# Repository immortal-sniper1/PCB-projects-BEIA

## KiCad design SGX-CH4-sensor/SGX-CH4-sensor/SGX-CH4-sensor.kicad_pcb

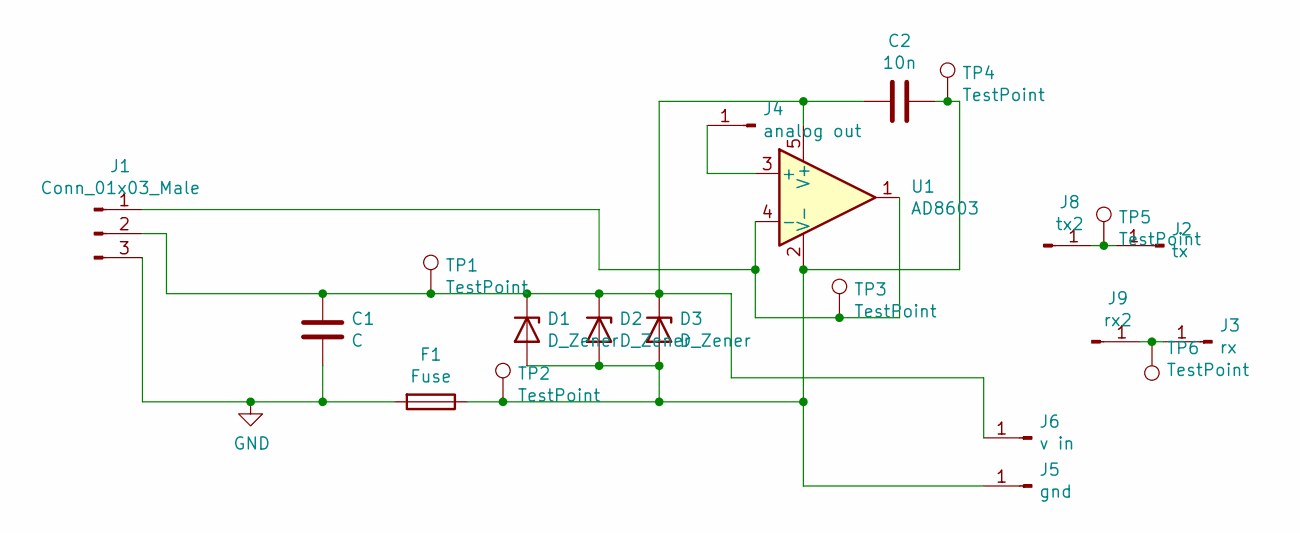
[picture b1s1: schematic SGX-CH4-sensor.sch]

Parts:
C1: C; CP_Radial_D8.0mm_P5.00mm
C2: 10n; CP_Radial_D6.3mm_P2.50mm
D1, D2, D3: D_Zener; D_DO-35_SOD27_P10.16mm_Horizontal
F1: Fuse; R_Axial_DIN0309_L9.0mm_D3.2mm_P5.08mm_Vertical
J1: Conn_01x03_Male; PinHeader_1x03_P2.54mm_Vertical
J2: tx; PinHeader_1x01_P2.54mm_Vertical
J3: rx; PinHeader_1x01_P2.54mm_Vertical
J4: analog out; PinHeader_1x01_P2.54mm_Vertical
J5: gnd; PinHeader_1x01_P2.54mm_Vertical
J6: v in; PinHeader_1x01_P2.54mm_Vertical
J8: tx2; PinHeader_1x01_P2.54mm_Vertical
J9: rx2; PinHeader_1x01_P2.54mm_Vertical
TP1, TP2, TP3, TP4, TP5, TP6: TestPoint; TestPoint_Pad_D3.0mm
U1: AD8603; SOT-23-5

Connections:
GND: C1.2, F1.2, J1.3
unnamed: C1.1, C2.1, D1.1 (K), D2.1 (K), D3.1 (K), J1.2, J6.1, TP1.1, U1.5 (V+)
unnamed: C2.2, D1.2 (A), D2.2 (A), D3.2 (A), F1.1, J5.1, TP2.1, TP4.1, U1.2 (V-)
unnamed: J1.1, TP3.1, U1.1, U1.4 (-)
unnamed: J2.1, J8.1, TP5.1
unnamed: J3.1, J9.1, TP6.1
unnamed: J4.1, U1.3 (+)

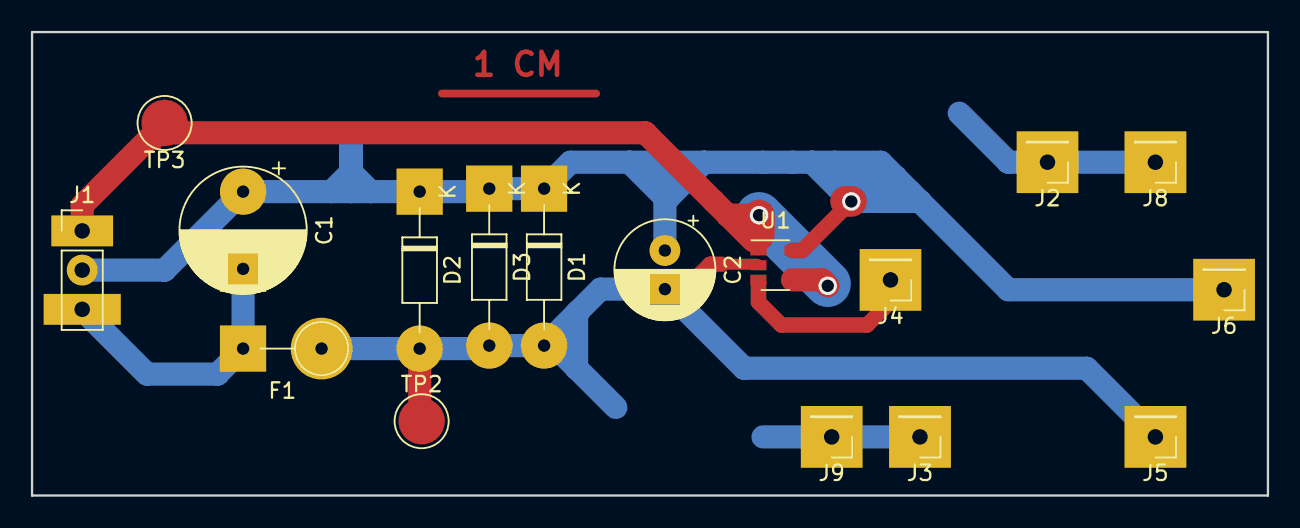
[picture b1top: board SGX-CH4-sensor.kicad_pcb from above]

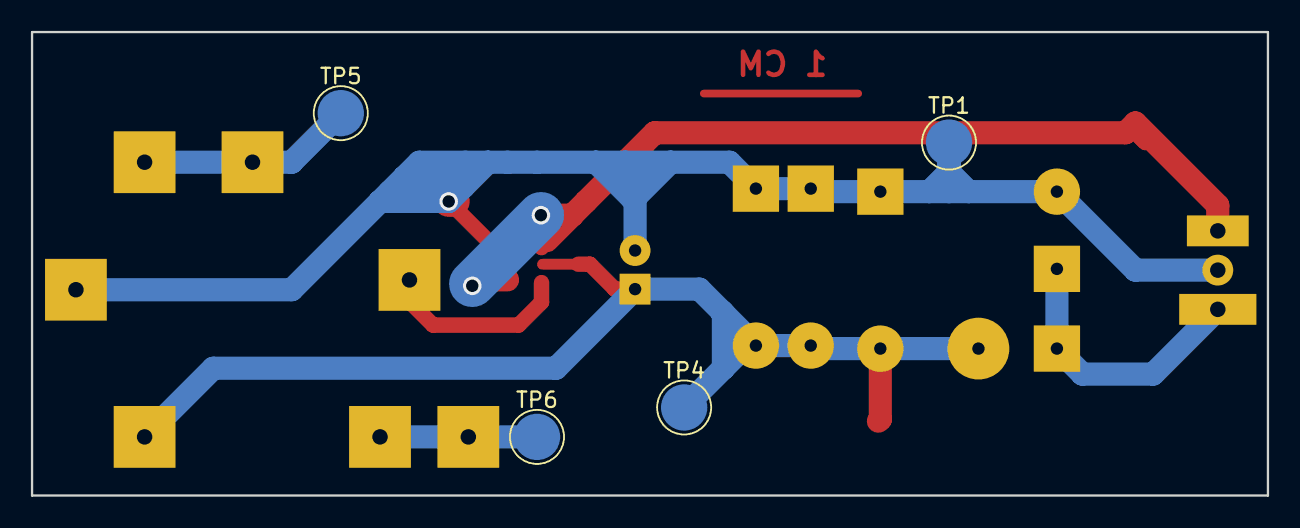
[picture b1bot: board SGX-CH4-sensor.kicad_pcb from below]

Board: 2 copper layers, 80.0 x 30.0 mm, 21 parts (4 on the bottom side), 7 nets.
